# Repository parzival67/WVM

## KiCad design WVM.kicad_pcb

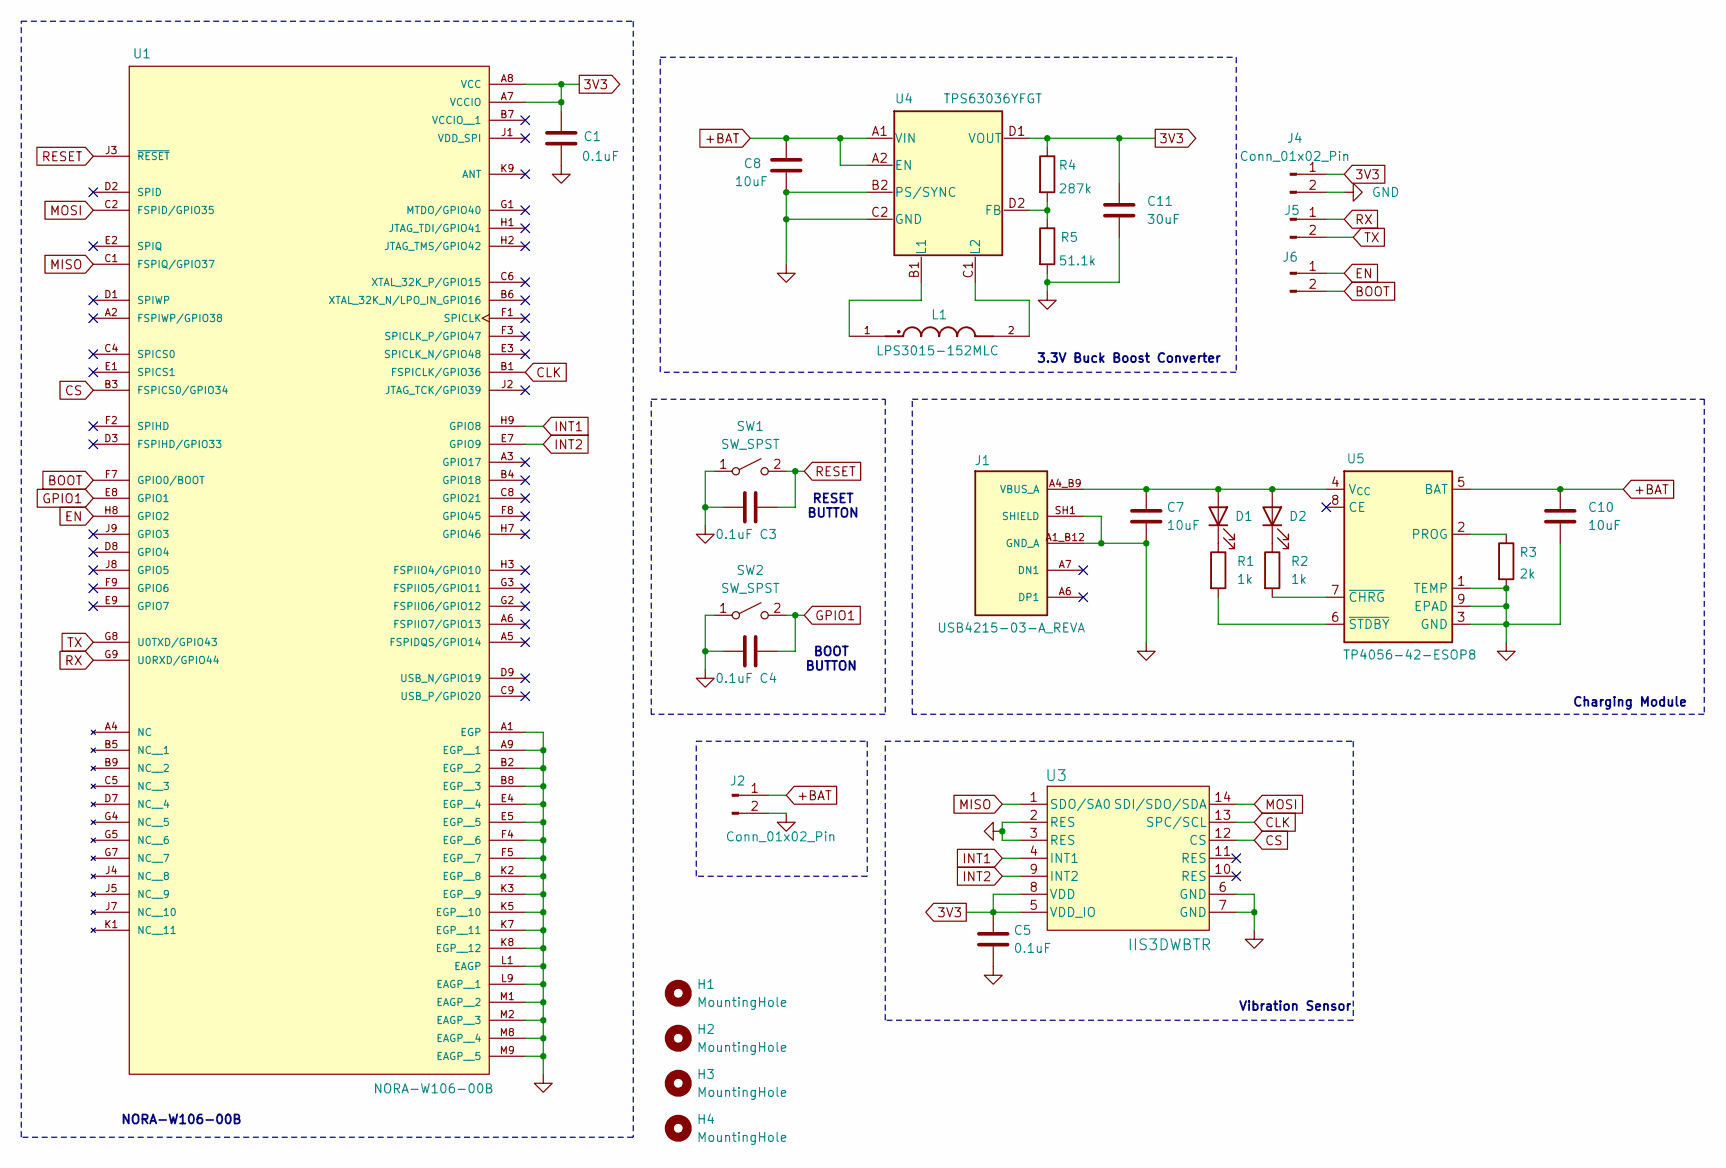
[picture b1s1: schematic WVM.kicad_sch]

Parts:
C1, C3, C4, C5: 0.1uF; C_0402_1005Metric
C7, C8, C10: 10uF; C_0402_1005Metric
C11: 30uF; C_0402_1005Metric
D1, D2: LED; LED_0402_1005Metric
H1, H2, H3, H4: MountingHole; MountingHole_2.2mm_M2_Pad_Via
J1: USB4215-03-A_REVA; PARTREV A
J2: Conn_01x02_Pin; Untitled
J4, J5, J6: Conn_01x02_Pin; PinHeader_1x02_P1.00mm_Vertical
L1: LPS3015-152MLC; IND_LPS3015-152MLC; PARTREV 12/13/21
R1, R2: 1k; R_0402_1005Metric
R3: 2k; R_0402_1005Metric
R4: 287k; R_0402_1005Metric
R5: 51.1k; R_0402_1005Metric
SW1, SW2: SW_SPST; SW_SPST_B3U-1000P
U1: NORA-W106-00B; XCVR_NORA-W106-00B; PARTREV R03
U3: IIS3DWBTR; LGA-14L_2P5X3X0P83_STM
U4: TPS63036YFGT
U5: TP4056-42-ESOP8; SOIC-8-1EP_3.9x4.9mm_P1.27mm_EP2.41x3.3mm_ThermalVias

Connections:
3V3: C1.1, C5.1, C11.1, J4.1, R4.1, U1.A7 (VCCIO), U1.A8 (VCC), U3.5 (VDD_IO), U3.8 (VDD), U4.D1 (VOUT)
+BAT: C8.1, C10.1, J2.1, U4.A1 (VIN), U4.A2 (EN), U5.5 (BAT)
BOOT: J6.2, U1.F7 (GPIO0/BOOT)
CLK: U1.B1 (FSPICLK/GPIO36), U3.13 (SPC/SCL)
CS: U1.B3 (FSPICS0/GPIO34), U3.12 (CS)
EN: J6.1, U1.H8 (GPIO2)
GND: C1.2, C3.1, C4.1, C5.2, C7.2, C8.2, C10.2, C11.2, J1.A1_B12 (GND_A), J1.SH1 (SHIELD), J2.2, J4.2, R3.2, R5.2, SW1.1 (A), SW2.1 (A), U1.A1 (EGP), U1.A9 (EGP__1), U1.B2 (EGP__2), U1.B8 (EGP__3), U1.E4 (EGP__4), U1.E5 (EGP__5), U1.F4 (EGP__6), U1.F5 (EGP__7), U1.K2 (EGP__8), U1.K3 (EGP__9), U1.K5 (EGP__10), U1.K7 (EGP__11), U1.K8 (EGP__12), U1.L1 (EAGP), U1.L9 (EAGP__1), U1.M1 (EAGP__2), U1.M2 (EAGP__3), U1.M8 (EAGP__4), U1.M9 (EAGP__5), U3.2 (RES), U3.3 (RES), U3.6 (GND), U3.7 (GND), U4.B2 (PS/SYNC), U4.C2 (GND), U5.1 (TEMP), U5.3 (GND), U5.9 (EPAD)
GPIO1: C4.2, SW2.2 (B), U1.E8 (GPIO1)
INT1: U1.H9 (GPIO8), U3.4 (INT1)
INT2: U1.E7 (GPIO9), U3.9 (INT2)
MISO: U1.C1 (FSPIQ/GPIO37), U3.1 (SDO/SA0)
MOSI: U1.C2 (FSPID/GPIO35), U3.14 (SDI/SDO/SDA)
unnamed: C7.1, D1.2 (A), D2.2 (A), J1.A4_B9 (VBUS_A), U5.4 (V_{CC})
unnamed: D1.1 (K), R1.1
unnamed: D2.1 (K), R2.1
unnamed: R4.2, R5.1, U4.D2 (FB)
unnamed: L1.1, U4.B1 (L1)
unnamed: L1.2, U4.C1 (L2)
unnamed: R3.1, U5.2 (PROG)
unnamed: R2.2, U5.7 (~CHRG)
unnamed: R1.2, U5.6 (~STDBY)
RESET: C3.2, SW1.2 (B), U1.J3 (~RESET)
RX: J5.1, U1.G9 (U0RXD/GPIO44)
TX: J5.2, U1.G8 (U0TXD/GPIO43)

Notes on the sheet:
Charging Module
BOOT BUTTON
Vibration Sensor
NORA-W106-00B
RESET BUTTON
3.3V Buck Boost Converter

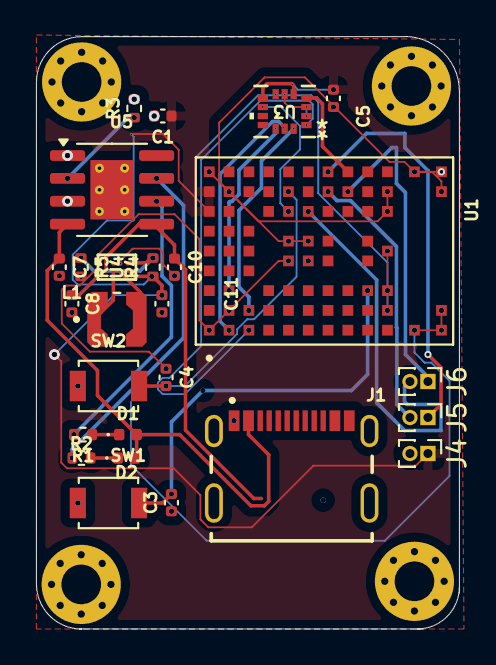
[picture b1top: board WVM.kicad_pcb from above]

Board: 2 copper layers, 23.5 x 32.9 mm, 31 parts (1 on the bottom side), 24 nets.

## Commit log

2025-10-08 Modified Schematic 07.10.25
2025-10-08 message
2025-10-09 cleaned schematic
2025-10-09 mesage
2025-10-09 Completed schematic 09.10.25
2025-10-09 09/08/2025
2025-10-10 10-10-2025
2025-10-13 Part Placement completed with board outline
2025-10-13 saved commit 13.10.25
2025-10-17 17102025
